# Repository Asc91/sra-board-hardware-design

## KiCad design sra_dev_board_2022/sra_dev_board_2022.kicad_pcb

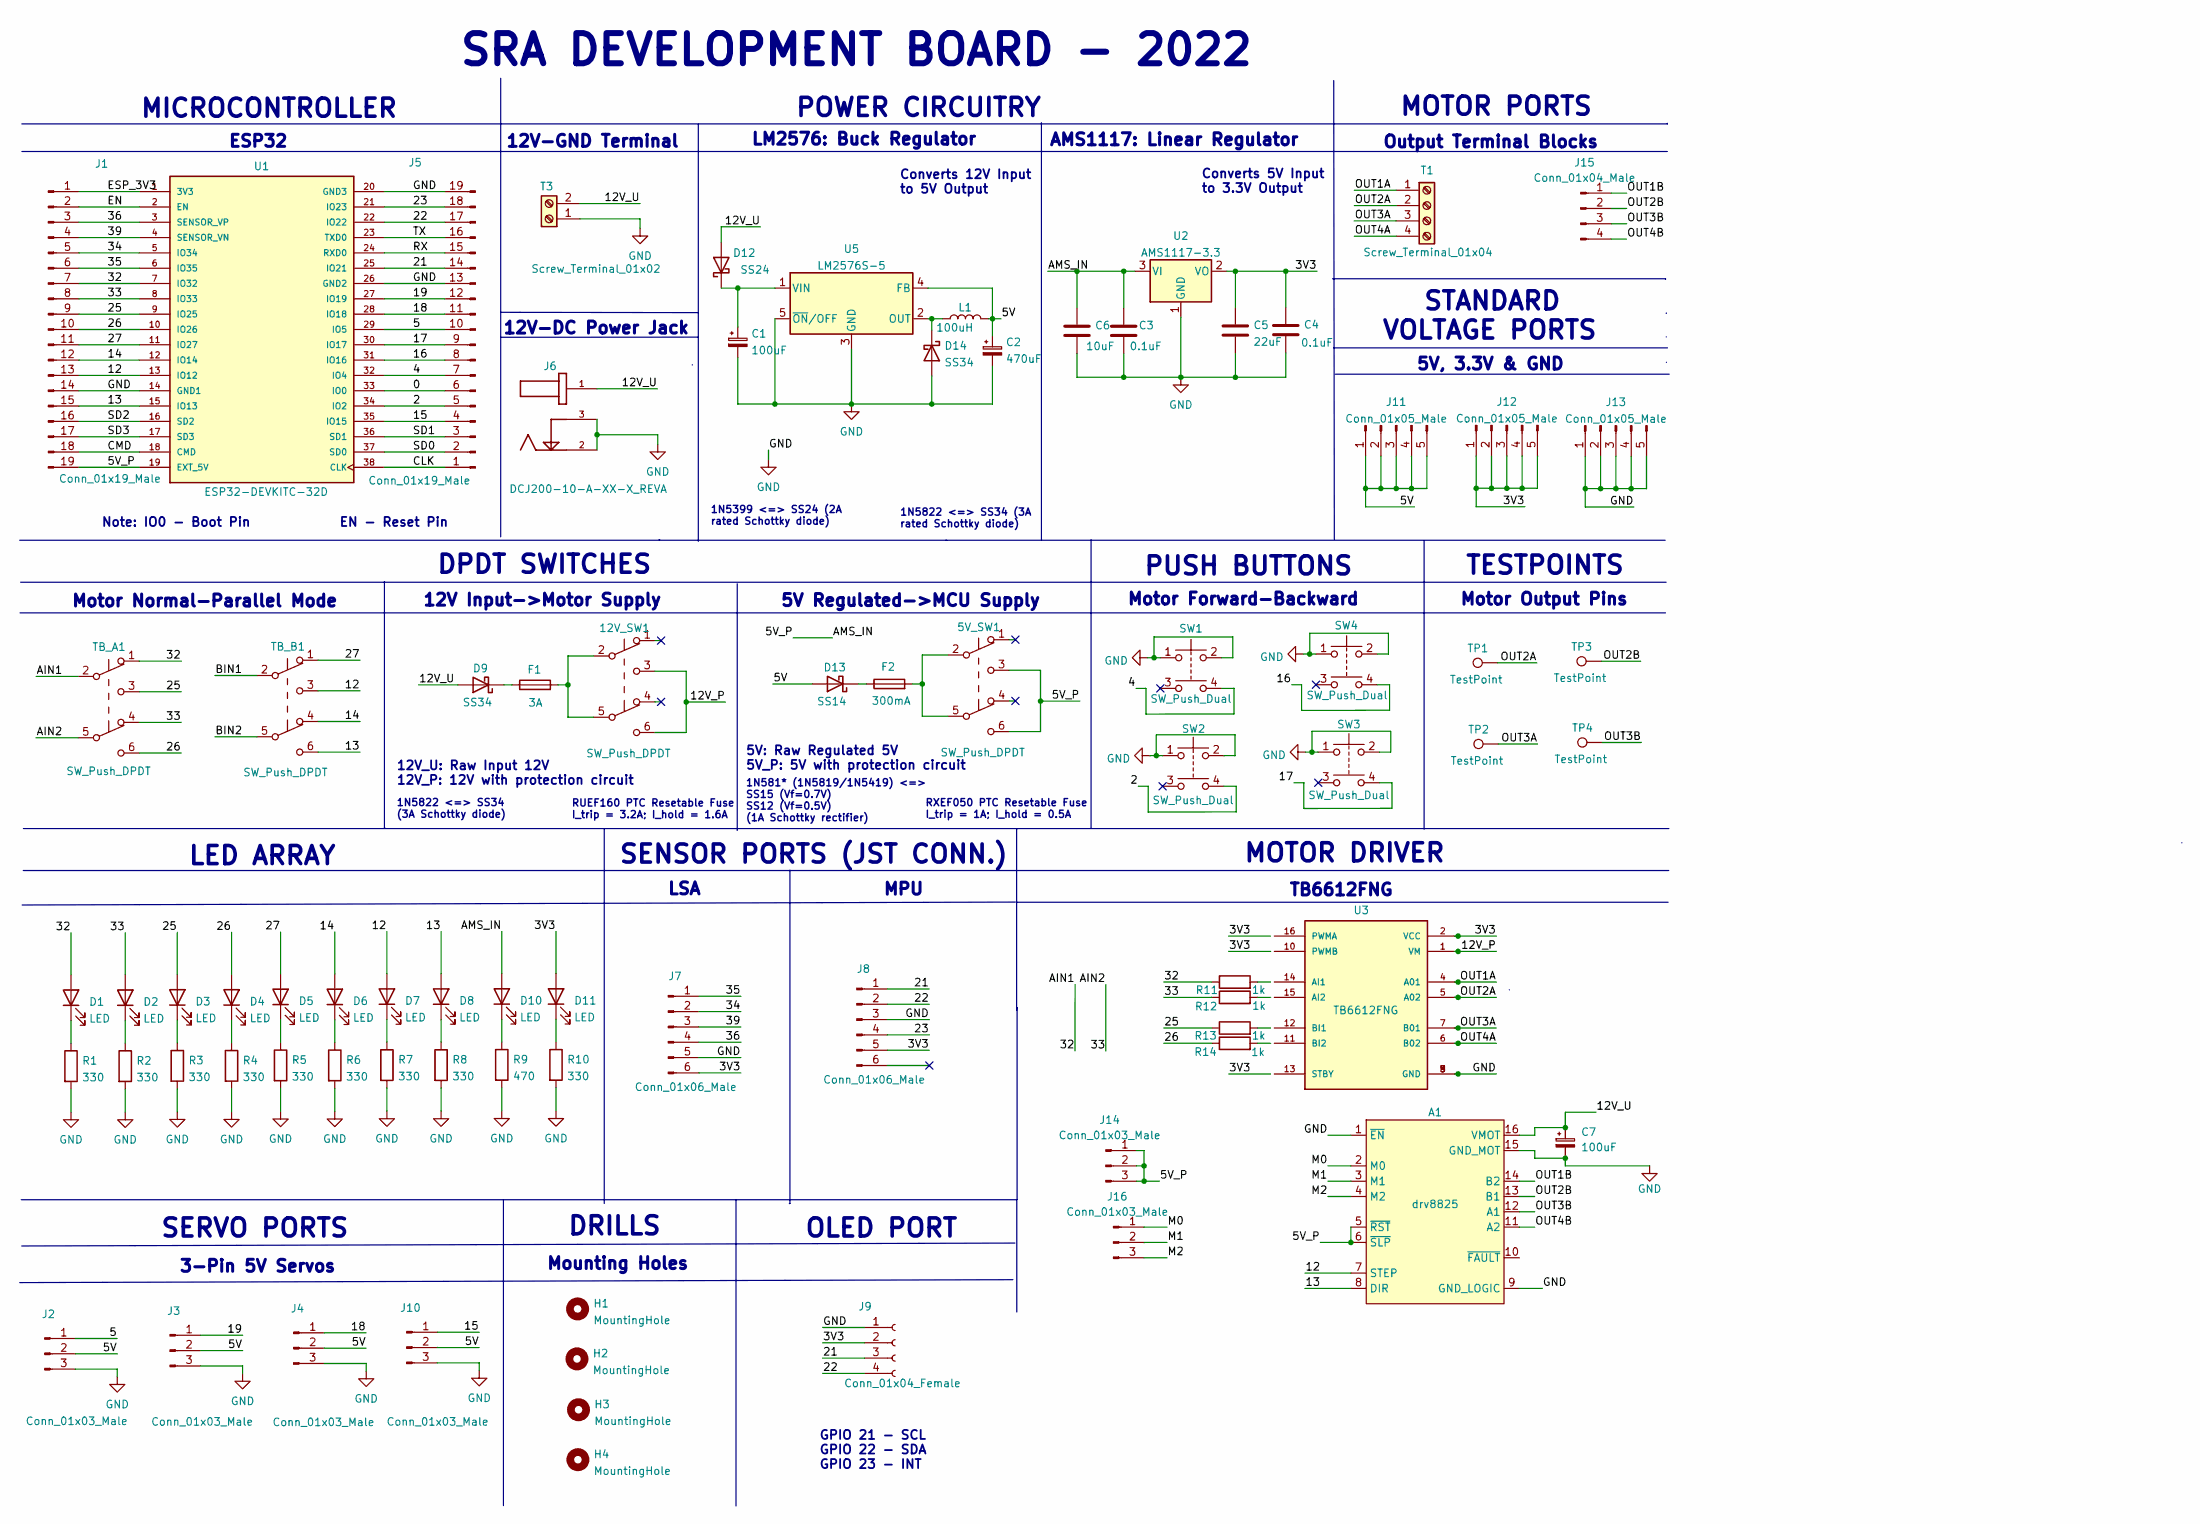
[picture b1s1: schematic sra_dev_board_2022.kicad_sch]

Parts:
5V_SW1, 12V_SW1: SW_Push_DPDT; dpdt_sw_2x03_tht
A1: drv8825; IC_DRV8825_STEPPER_MOTOR_DRIVER_CARRIER
C1, C7: 100uF; CP_Elec_6.3x7.7
C2: 470uF; CP_Elec_8x10
C3, C4: 0.1uF; C_0603_1608Metric
C5: 22uF; C_0603_1608Metric
C6: 10uF; C_0603_1608Metric
D1, D2, D3, D4, D5, D6, D7, D8, D10, D11: LED; LED_0603_1608Metric
D9, D14: SS34; D_SMB
D12: SS24; D_SMA
D13: SS14; D_SMA
F1: 3A; RUEF160
F2: 300mA; RXEF050
H1, H2, H3, H4: MountingHole; MountingHole_3.2mm_M3
J1, J5: Conn_01x19_Male; 1X19
J2, J3, J4, J10: Conn_01x03_Male; 1X03
J6: DCJ200-10-A-XX-X_REVA; BarrelJack_Wuerth_6941xx301002
J7, J8: Conn_01x06_Male; PinHeader_1x06_P2.54mm_Vertical
J9: Conn_01x04_Female; 1X04
J11, J12, J13: Conn_01x05_Male; 1X05
J14, J16: Conn_01x03_Male; PinHeader_1x03_P2.54mm_Vertical
J15: Conn_01x04_Male; PinHeader_1x04_P2.54mm_Vertical
L1: 100uH; CDRH127_inductor_smd
R1, R2, R3, R4, R5, R6, R7, R8, R10: 330; R_0603_1608Metric
R9: 470; R_0603_1608Metric
R11, R12, R13, R14: 1k; R_1206_3216Metric
SW1, SW2, SW3, SW4: SW_Push_Dual; spst_tactile_sw_2x02_smd
T1: Screw_Terminal_01x04; motor_1x04_tht
T3: Screw_Terminal_01x02; 12V_1x02_tht
TB_A1: SW_Push_DPDT; dpdt_sw_2x03_tht
TB_B1: SW_Push_DPDT; dpdt_sw_2x03_tht
TP1, TP2, TP3, TP4: TestPoint; pad_1,27-2,54_smd
U1: ESP32-DEVKITC-32D; ESP32-DEVKITCv4-32D; PARTREV 4
U2: AMS1117-3.3; SOT-223-3_TabPin2
U3: TB6612FNG; TB6612FNG_2; PARTREV 11-13-17
U5: LM2576S-5; TO-263-5_TabPin3

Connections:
/0: J5.6, U1.33 (IO0)
/2: J5.5, SW2.4, U1.34 (IO2)
/3V3: C4.1, C5.1, D11.2 (A), J7.6, J8.5, J9.2, J12.1, J12.2, J12.3, J12.4, J12.5, U2.2 (VO), U3.2 (VCC)
/4: J5.7, SW1.4, U1.32 (IO4)
/5: J2.1, J5.10, U1.29 (IO5)
/5V: C2.1, D13.2 (A), J2.2, J3.2, J4.2, J10.2, J11.1, J11.2, J11.3, J11.4, J11.5, L1.2, U5.4 (FB)
/5V_P: 5V_SW1.3 (C), 5V_SW1.6 (C), A1.5 (~RST), A1.6 (~SLP), C3.1, C6.1, D10.2 (A), J1.19, J14.1, J14.2, J14.3, U1.19 (EXT_5V), U2.3 (VI)
/12: A1.7 (STEP), D7.2 (A), J1.13, TB_B1.3 (C), U1.13 (IO12)
/12V_P: 12V_SW1.3 (C), 12V_SW1.6 (C), U3.1 (VM)
/12V_U: A1.16 (VMOT), C7.1, D9.2 (A), D12.2 (A), J6.1, T3.2
/13: A1.8 (DIR), D8.2 (A), J1.15, TB_B1.6 (C), U1.15 (IO13)
/14: D6.2 (A), J1.12, TB_B1.4 (A), U1.12 (IO14)
/15: J5.4, J10.1, U1.35 (IO15)
/16: J5.8, SW4.4, U1.31 (IO16)
/17: J5.9, SW3.4, U1.30 (IO17)
/18: J4.1, J5.11, U1.28 (IO18)
/19: J3.1, J5.12, U1.27 (IO19)
/21: J5.14, J8.1, J9.3, U1.25 (IO21)
/22: J5.17, J8.2, J9.4, U1.22 (IO22)
/23: J5.18, J8.4, U1.21 (IO23)
/25: D3.2 (A), J1.9, R13.1, TB_A1.3 (C), U1.9 (IO25)
/26: D4.2 (A), J1.10, R14.1, TB_A1.6 (C), U1.10 (IO26)
/27: D5.2 (A), J1.11, TB_B1.1 (A), U1.11 (IO27)
/32: D1.2 (A), J1.7, R11.1, TB_A1.1 (A), TB_A1.2 (B), U1.7 (IO32)
/33: D2.2 (A), J1.8, R12.1, TB_A1.4 (A), TB_A1.5 (B), U1.8 (IO33)
/34: J1.5, J7.2, U1.5 (IO34)
/35: J1.6, J7.1, U1.6 (IO35)
/36: J1.3, J7.4, U1.3 (SENSOR_VP)
/39: J1.4, J7.3, U1.4 (SENSOR_VN)
/BIN1: TB_B1.2 (B)
/BIN2: TB_B1.5 (B)
/CLK: J5.1, U1.38 (CLK)
/CMD: J1.18, U1.18 (CMD)
/EN: J1.2, U1.2 (EN)
/ESP_3V3: J1.1, U1.1 (3V3)
/M0: A1.2 (M0), J16.1
/M1: A1.3 (M1), J16.2
/M2: A1.4 (M2), J16.3
/OUT1A: T1.1, U3.4 (A01)
/OUT1B: A1.14 (B2), J15.1
/OUT2A: T1.2, TP1.1, U3.5 (A02)
/OUT2B: A1.13 (B1), J15.2, TP3.1
/OUT3A: T1.3, TP2.1, U3.7 (B01)
/OUT3B: A1.12 (A1), J15.3, TP4.1
/OUT4A: T1.4, U3.6 (B02)
/OUT4B: A1.11 (A2), J15.4
/RX: J5.15, U1.24 (RXD0)
/SD0: J5.2, U1.37 (SD0)
/SD1: J5.3, U1.36 (SD1)
/SD2: J1.16, U1.16 (SD2)
/SD3: J1.17, U1.17 (SD3)
/TX: J5.16, U1.23 (TXD0)
GND: A1.1 (~EN), A1.9 (GND_LOGIC), A1.15 (GND_MOT), C1.2, C2.2, C3.2, C4.2, C5.2, C6.2, C7.2, D14.2 (A), J1.14, J2.3, J3.3, J4.3, J5.13, J5.19, J6.2, J6.3, J7.5, J8.3, J9.1, J10.3, J13.1, J13.2, J13.3, J13.4, J13.5, R1.2, R2.2, R3.2, R4.2, R5.2, R6.2, R7.2, R8.2, R9.2, R10.2, SW1.1, SW1.2, SW2.1, SW2.2, SW3.1, SW3.2, SW4.1, SW4.2, T3.1, U1.14 (GND1), U1.20 (GND3), U1.26 (GND2), U2.1 (GND), U3.3 (GND), U3.8 (GND), U3.9 (GND), U5.3 (GND), U5.5 (~ON/OFF)
unnamed: 5V_SW1.2 (B), 5V_SW1.5 (B), F2.2
unnamed: 12V_SW1.2 (B), 12V_SW1.5 (B), F1.2
unnamed: C1.1, D12.1 (K), U5.1 (VIN)
unnamed: D1.1 (K), R1.1
unnamed: D2.1 (K), R2.1
unnamed: D3.1 (K), R3.1
unnamed: D4.1 (K), R4.1
unnamed: D5.1 (K), R5.1
unnamed: D6.1 (K), R6.1
unnamed: D7.1 (K), R7.1
unnamed: D8.1 (K), R8.1
unnamed: D9.1 (K), F1.1
unnamed: D10.1 (K), R9.1
unnamed: D11.1 (K), R10.1
unnamed: D13.1 (K), F2.1
unnamed: D14.1 (K), L1.1, U5.2 (OUT)

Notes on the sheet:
5V, 3.3V & GND
RXEF050 PTC Resetable Fuse I_trip = 1A; I_hold = 0.5A
Mounting Holes
SRA DEVELOPMENT BOARD - 2022
LED ARRAY
12V_U: Raw Input 12V 12V_P: 12V with protection circuit
12V-GND Terminal
1N5822 <=> SS34 (3A rated Schottky diode)
Output Terminal Blocks
LSA
MPU
Converts 5V Input to 3.3V Output
DRILLS
SENSOR PORTS (JST CONN.)
1N5399 <=> SS24 (2A rated Schottky diode)
DPDT SWITCHES
5V: Raw Regulated 5V 5V_P: 5V with protection circuit
Note: IO0 - Boot Pin EN - Reset Pin
POWER CIRCUITRY
ESP32
RUEF160 PTC Resetable Fuse I_trip = 3.2A; I_hold = 1.6A
LM2576: Buck Regulator
MICROCONTROLLER
GPIO 21 - SCL GPIO 22 - SDA GPIO 23 - INT
TB6612FNG
1N5822 <=> SS34 (3A Schottky diode)
3-Pin 5V Servos
SERVO PORTS
1N581* (1N5819/1N5419) <=> SS15 (Vf=0.7V) SS12 (Vf=0.5V) (1A Schottky rectifier)
12V Input->Motor Supply
5V Regulated->MCU Supply
OLED PORT
MOTOR PORTS
Motor Output Pins
MOTOR DRIVER
12V-DC Power Jack
Converts 12V Input to 5V Output
TESTPOINTS
PUSH BUTTONS
Motor Forward-Backward

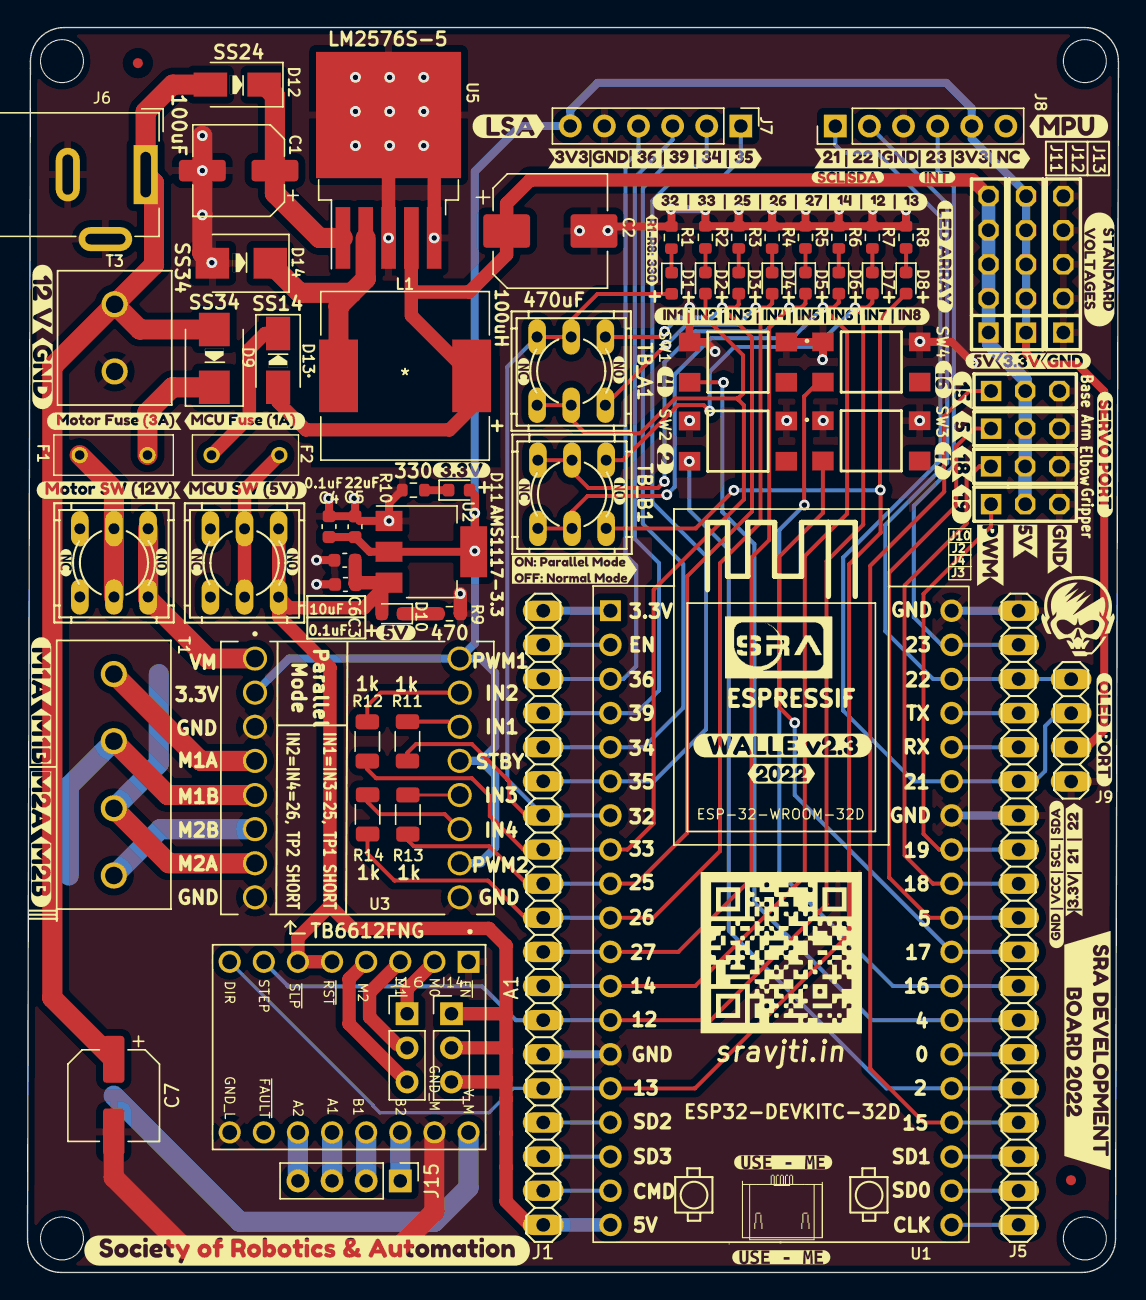
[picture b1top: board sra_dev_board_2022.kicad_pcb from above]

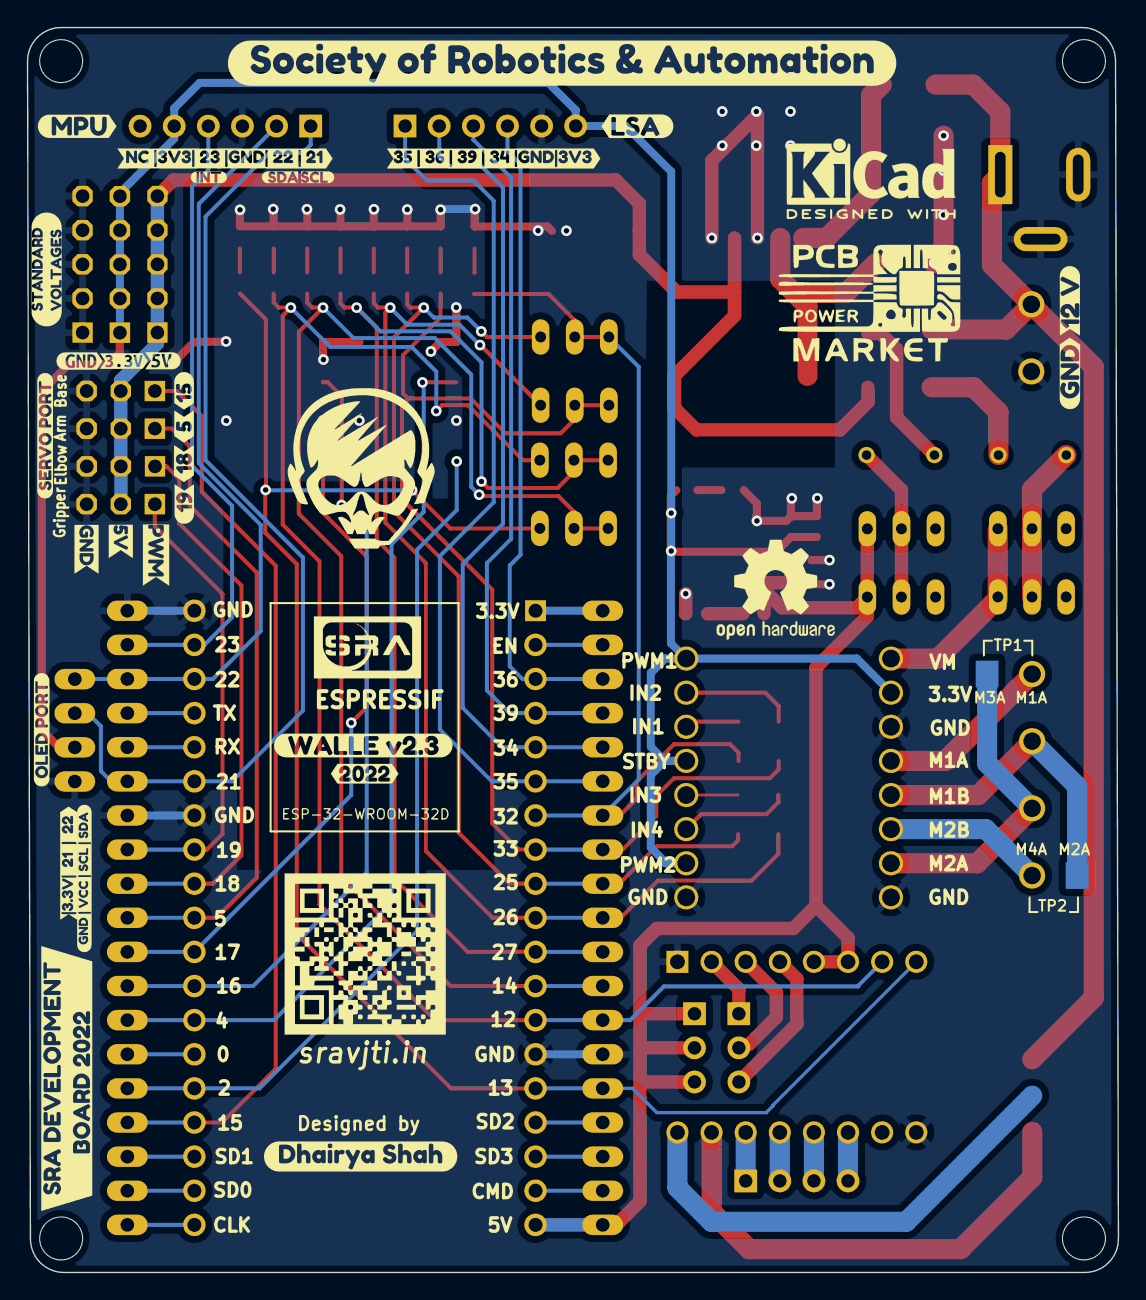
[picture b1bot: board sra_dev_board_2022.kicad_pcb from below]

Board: 2 copper layers, 81.2 x 92.7 mm, 165 parts (29 on the bottom side), 67 nets.

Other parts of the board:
kibuzzard-61F6A2E5, kibuzzard-61F6A2E5#2: G***; kibuzzard-61F6A2E5
kibuzzard-61F6A04D: G***; kibuzzard-61F6A04D
kibuzzard-61F6A06B: G***; kibuzzard-61F6A06B
kibuzzard-61F6A6E8, kibuzzard-61F6A6E8#2: G***; kibuzzard-61F6A6E8
kibuzzard-61F6A036: G***; kibuzzard-61F6A036
kibuzzard-61F6A088: G***; kibuzzard-61F6A088
kibuzzard-61F6A786, kibuzzard-61F6A786#2: G***; kibuzzard-61F6A786
kibuzzard-61F6ABAB, kibuzzard-61F6ABAB#2: G***; kibuzzard-61F6ABAB
kibuzzard-61F6AD1B, kibuzzard-61F6AD1B#2: G***; kibuzzard-61F6AD1B
kibuzzard-61F6AD42, kibuzzard-61F6AD42#2: G***; kibuzzard-61F6AD42
kibuzzard-61F6B85D: G***; kibuzzard-61F6B85D
kibuzzard-61F6B86D: G***; kibuzzard-61F6B86D
kibuzzard-61F6B851: G***; kibuzzard-61F6B851
kibuzzard-61F6B878: G***; kibuzzard-61F6B878
kibuzzard-61F7BB7D: G***; kibuzzard-61F7BB7D
kibuzzard-61F7C0C2: G***; kibuzzard-61F7C0C2
kibuzzard-61F7C0CC: G***; kibuzzard-61F7C0CC
kibuzzard-61F7C05B: G***; kibuzzard-61F7C05B
kibuzzard-61F7C12E: G***; kibuzzard-61F7C12E
kibuzzard-61F7C21A: G***; kibuzzard-61F7C21A
kibuzzard-61F7C24F, kibuzzard-61F7C24F#2: G***; kibuzzard-61F7C24F
kibuzzard-61F7C221: G***; kibuzzard-61F7C221
kibuzzard-61F7CB17: G***; kibuzzard-61F7CB17
kibuzzard-61F7D5C6: G***; kibuzzard-61F7D5C6
kibuzzard-61F7D60F: G***; kibuzzard-61F7D60F
kibuzzard-61F7D817: G***; kibuzzard-61F7D817
kibuzzard-61F7D852: G***; kibuzzard-61F7D852
kibuzzard-61F7E9C0: G***; kibuzzard-61F7E9C0
kibuzzard-61F7EB28: G***; kibuzzard-61F7EB28
kibuzzard-61F7EC8D: G***; kibuzzard-61F7EC8D
kibuzzard-61F7EC33: G***; kibuzzard-61F7EC33
kibuzzard-61F7EC75: G***; kibuzzard-61F7EC75
kibuzzard-61F7ED8A: G***; kibuzzard-61F7ED8A
kibuzzard-61F7ED72: G***; kibuzzard-61F7ED72
kibuzzard-61F7EDAC: G***; kibuzzard-61F7EDAC
kibuzzard-61F7EDC6: G***; kibuzzard-61F7EDC6
kibuzzard-61F7EF48: G***; kibuzzard-61F7EF48
kibuzzard-61F7EFEB: G***; kibuzzard-61F7EFEB
kibuzzard-61F7FB1D: G***; kibuzzard-61F7FB1D
kibuzzard-61F7FBA3: G***; kibuzzard-61F7FBA3
kibuzzard-61F7FBC2: G***; kibuzzard-61F7FBC2
kibuzzard-61F67ED2, kibuzzard-61F67ED2#2: G***; kibuzzard-61F67ED2
kibuzzard-61F683BD, kibuzzard-61F683BD#2, kibuzzard-61F683BD#3, kibuzzard-61F683BD#4: G***; kibuzzard-61F683BD
kibuzzard-61F712A9: G***; kibuzzard-61F712A9
kibuzzard-61F792D2, kibuzzard-61F792D2#2: G***; kibuzzard-61F792D2
kibuzzard-61F793BD: G***; kibuzzard-61F793BD
kibuzzard-61F6808A, kibuzzard-61F6808A#2: G***; kibuzzard-61F6808A
kibuzzard-61F7105E: G***; kibuzzard-61F7105E
kibuzzard-61F7127D: G***; kibuzzard-61F7127D
kibuzzard-61F7147A: G***; kibuzzard-61F7147A
kibuzzard-61F8332E: G***; kibuzzard-61F8332E
kibuzzard-61F71050: G***; kibuzzard-61F71050
kibuzzard-61F71139, kibuzzard-61F71139#2: G***; kibuzzard-61F71139
kibuzzard-61F71200: G***; kibuzzard-61F71200
kibuzzard-61F71294: G***; kibuzzard-61F71294
kibuzzard-61F71491: G***; kibuzzard-61F71491
kibuzzard-61F79319, kibuzzard-61F79319#2: G***; kibuzzard-61F79319
kibuzzard-61F82282: G***; kibuzzard-61F82282
kibuzzard-61F83333: G***; kibuzzard-61F83333
kibuzzard-620CE59A: G***; kibuzzard-620CE59A
kibuzzard-620D3ACF, kibuzzard-620D3ACF#2: G***; kibuzzard-620D3ACF
kibuzzard-620D3AFB, kibuzzard-620D3AFB#2: G***; kibuzzard-620D3AFB
kibuzzard-620D3FD3, kibuzzard-620D3FD3#2: G***; kibuzzard-620D3FD3
kibuzzard-620D3FE5: G***; kibuzzard-620D3FE5
kibuzzard-620D4F5E: G***; kibuzzard-620D4F5E
kibuzzard-620D4F84: G***; kibuzzard-620D4F84
kibuzzard-620D363E: G***; kibuzzard-620D363E
kibuzzard-620D404F: G***; kibuzzard-620D404F
kibuzzard-620D3625: G***; kibuzzard-620D3625
kibuzzard-620D3646: G***; kibuzzard-620D3646
kibuzzard-620D4024, kibuzzard-620D4024#2: G***; kibuzzard-620D4024

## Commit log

2022-10-26 Added drv8825 stepper motor driver

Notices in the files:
parts and their libraries:
Copyright 2021 Accelerated Designs. All rights reserved.
